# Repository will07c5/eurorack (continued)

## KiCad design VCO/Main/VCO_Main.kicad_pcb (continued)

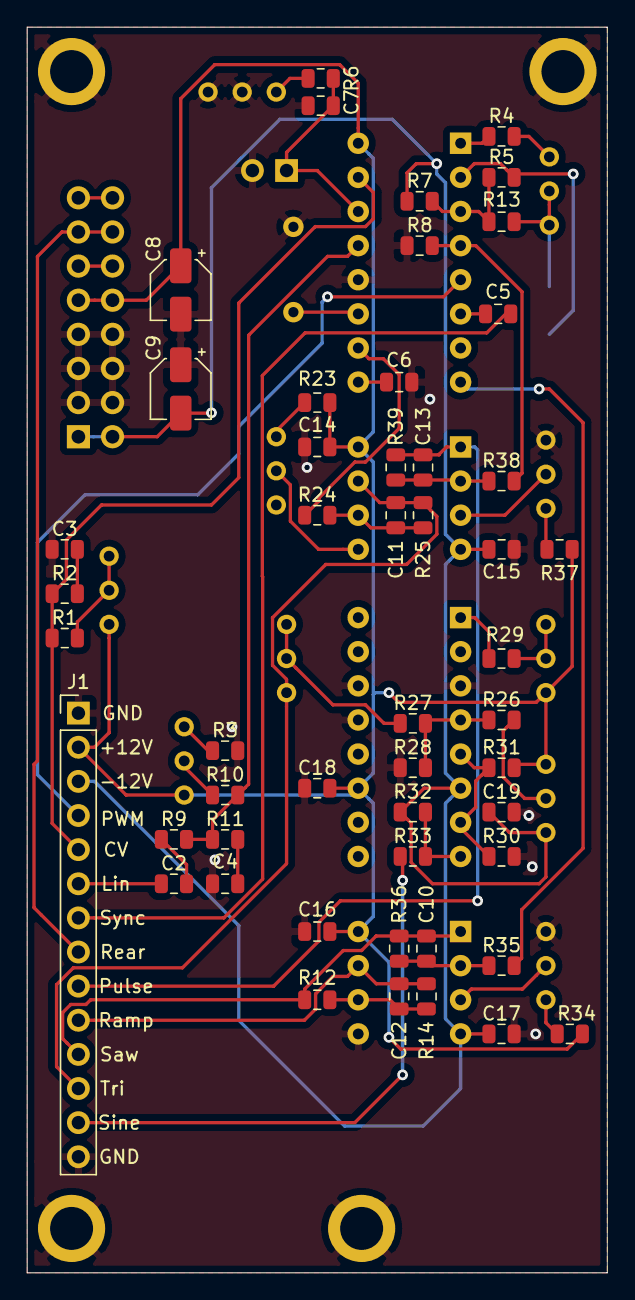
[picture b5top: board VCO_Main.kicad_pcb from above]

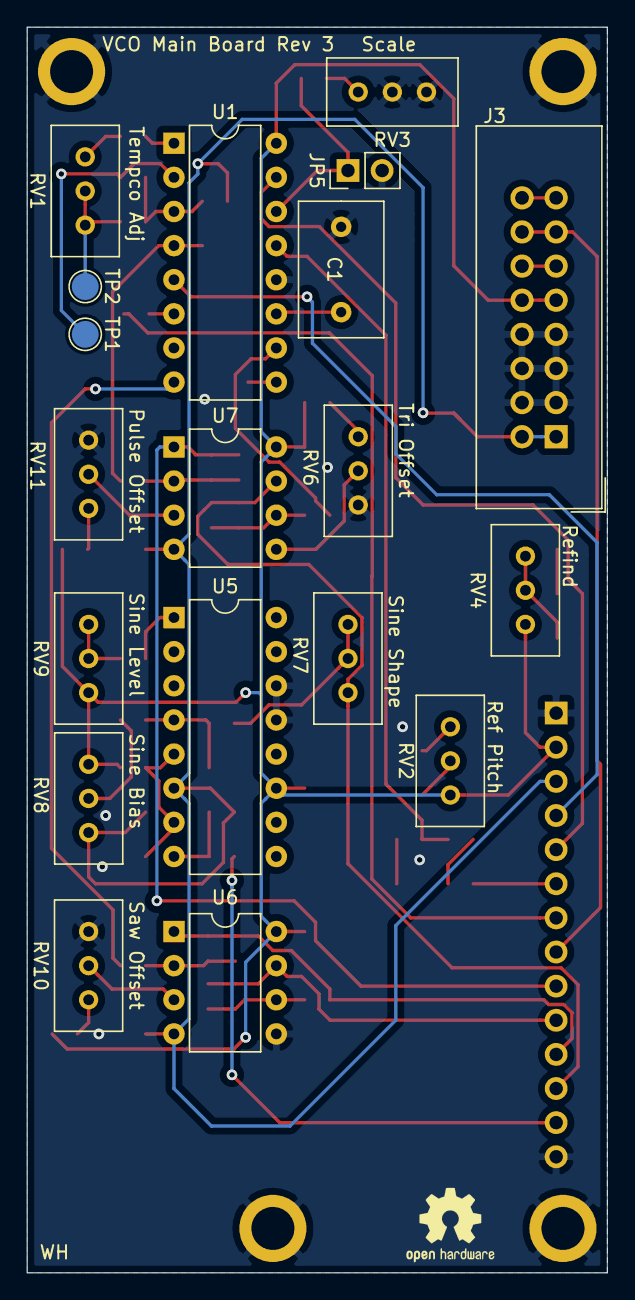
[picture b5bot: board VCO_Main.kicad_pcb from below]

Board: 2 copper layers, 43.2 x 92.7 mm, 73 parts (19 on the bottom side), 52 nets.

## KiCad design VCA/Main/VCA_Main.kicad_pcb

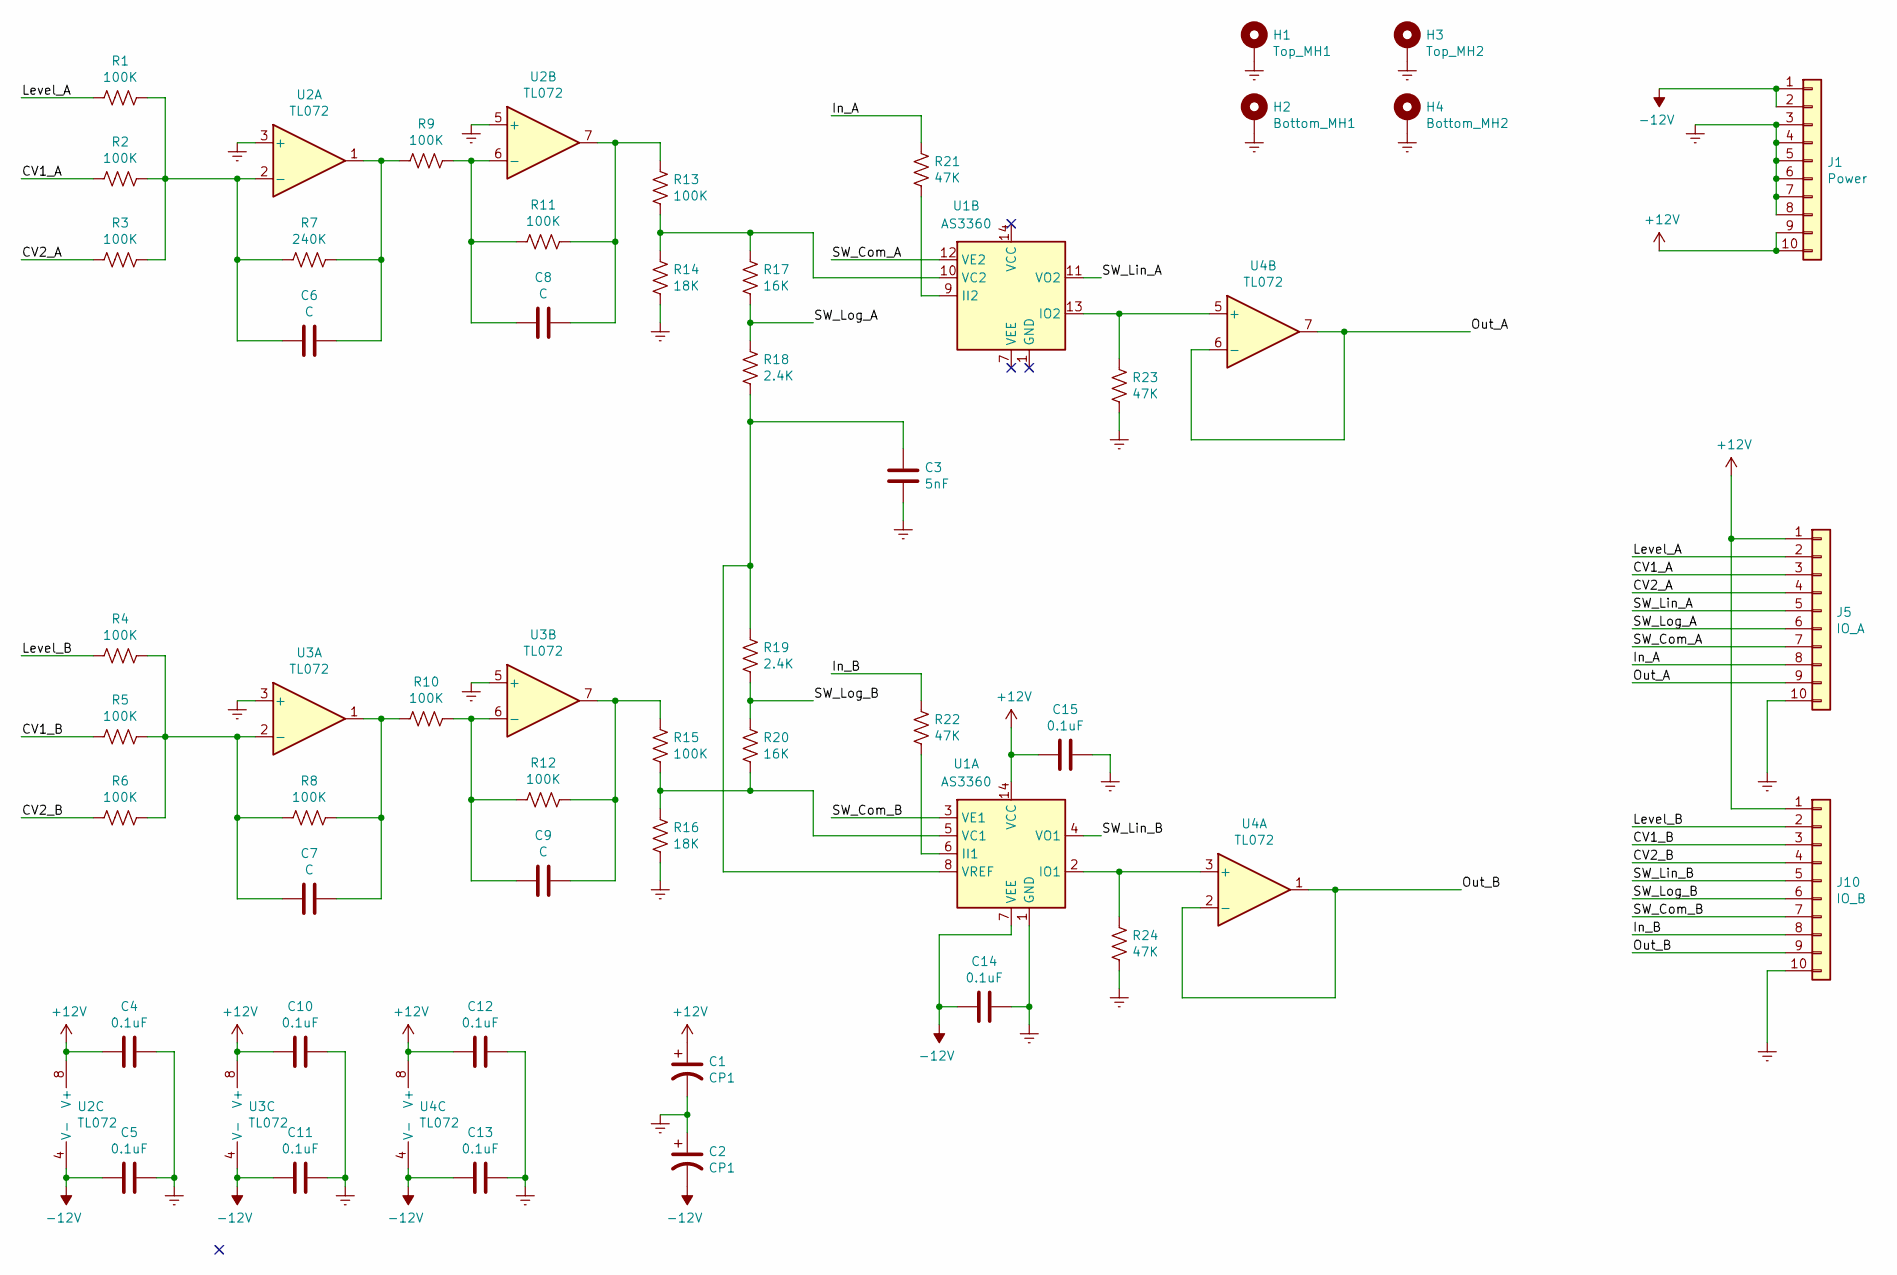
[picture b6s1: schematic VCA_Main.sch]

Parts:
C1, C2: CP1; CP_Elec_4x3
C3: 5nF; C_0805_2012Metric
C4, C5, C10, C11, C12, C13, C14, C15: 0.1uF; C_0805_2012Metric
C6, C7, C8, C9: C; C_0805_2012Metric
H1: Top_MH1; eurorack_mounting_hole
H2: Bottom_MH1; eurorack_mounting_hole
H3: Top_MH2; eurorack_mounting_hole
H4: Bottom_MH2; eurorack_mounting_hole
J1: Power; IDC-Header_2x05_P2.54mm_Vertical
J5: IO_A; PinHeader_1x10_P2.54mm_Vertical
J10: IO_B; PinHeader_1x10_P2.54mm_Vertical
R1, R2, R3, R4, R5, R6, R8, R9, R10, R11, R12, R13, R15: 100K; R_0805_2012Metric
R7: 240K; R_0805_2012Metric
R14, R16: 18K; R_0805_2012Metric
R17, R20: 16K; R_0805_2012Metric
R18, R19: 2.4K; R_0805_2012Metric
R21, R22, R23, R24: 47K; R_0805_2012Metric
U1: AS3360; DIP-14_W7.62mm
U2, U3, U4: TL072; DIP-8_W7.62mm

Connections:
+12V: C1.1, C4.2, C10.2, C12.2, C15.2, J1.9, J1.10, J5.1, J10.1, U1.14 (VCC), U2.8 (V+), U3.8 (V+), U4.8 (V+)
-12V: C2.2, C5.2, C11.2, C13.2, C14.2, J1.1, J1.2, U1.7 (VEE), U2.4 (V-), U3.4 (V-), U4.4 (V-)
/CV1_A: J5.3, R2.2
/CV1_B: J10.3, R5.2
/CV2_A: J5.4, R3.2
/CV2_B: J10.4, R6.2
/In_A: J5.8, R21.1
/In_B: J10.8, R22.1
/Level_A: J5.2, R1.2
/Level_B: J10.2, R4.2
/Out_A: J5.9, U4.6 (-), U4.7
/Out_B: J10.9, U4.1, U4.2 (-)
/SW_Com_A: J5.7, U1.12 (VE2)
/SW_Com_B: J10.7, U1.3 (VE1)
/SW_Lin_A: J5.5, U1.11 (VO2)
/SW_Lin_B: J10.5, U1.4 (VO1)
/SW_Log_A: J5.6, R17.2, R18.1
/SW_Log_B: J10.6, R19.2, R20.1
GNDREF: C1.2, C2.1, C3.2, C4.1, C5.1, C10.1, C11.1, C12.1, C13.1, C14.1, C15.1, H1.1, H2.1, H3.1, H4.1, J1.3, J1.4, J1.5, J1.6, J1.7, J1.8, J5.10, J10.10, R14.2, R16.2, R23.2, R24.2, U1.1 (GND), U2.3 (+), U2.5 (+), U3.3 (+), U3.5 (+)
unnamed: C3.1, R18.2, R19.1, U1.8 (VREF)
unnamed: C6.1, R7.1, R9.2, U2.1
unnamed: C6.2, R1.1, R2.1, R3.1, R7.2, U2.2 (-)
unnamed: C7.1, R8.1, R10.2, U3.1
unnamed: C7.2, R4.1, R5.1, R6.1, R8.2, U3.2 (-)
unnamed: C8.1, R11.1, R13.1, U2.7
unnamed: C8.2, R9.1, R11.2, U2.6 (-)
unnamed: C9.1, R12.1, R15.1, U3.7
unnamed: C9.2, R10.1, R12.2, U3.6 (-)
unnamed: R13.2, R14.1, R17.1, U1.10 (VC2)
unnamed: R15.2, R16.1, R20.2, U1.5 (VC1)
unnamed: R21.2, U1.9 (II2)
unnamed: R22.2, U1.6 (II1)
unnamed: R23.1, U1.13 (IO2), U4.5 (+)
unnamed: R24.1, U1.2 (IO1), U4.3 (+)

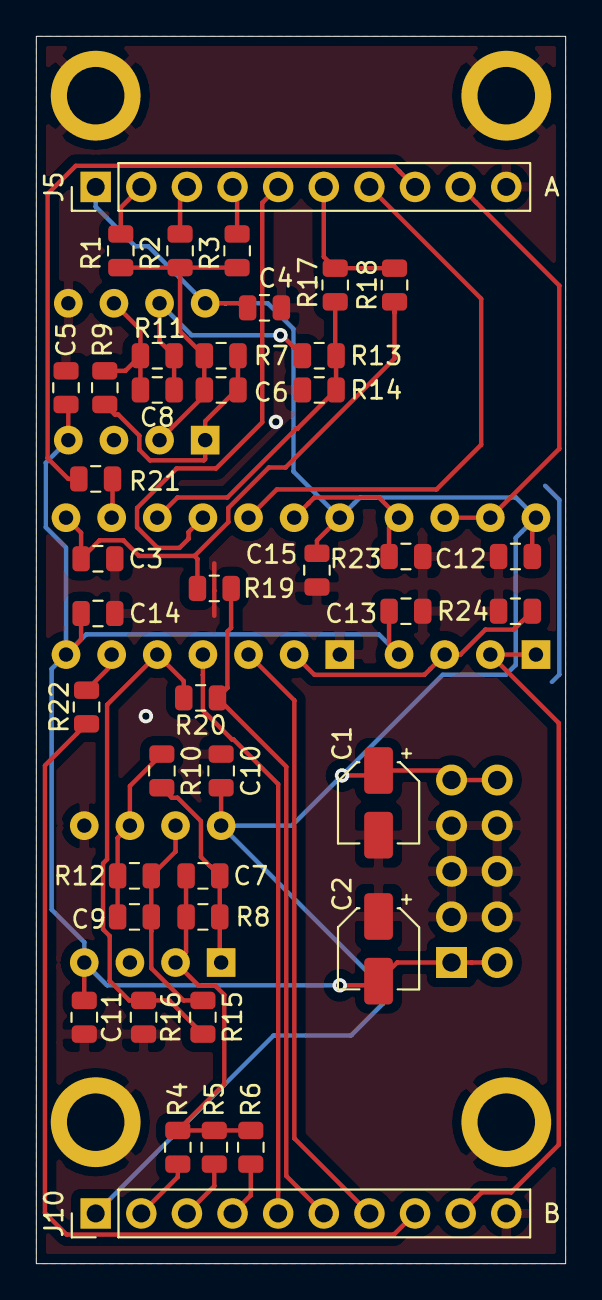
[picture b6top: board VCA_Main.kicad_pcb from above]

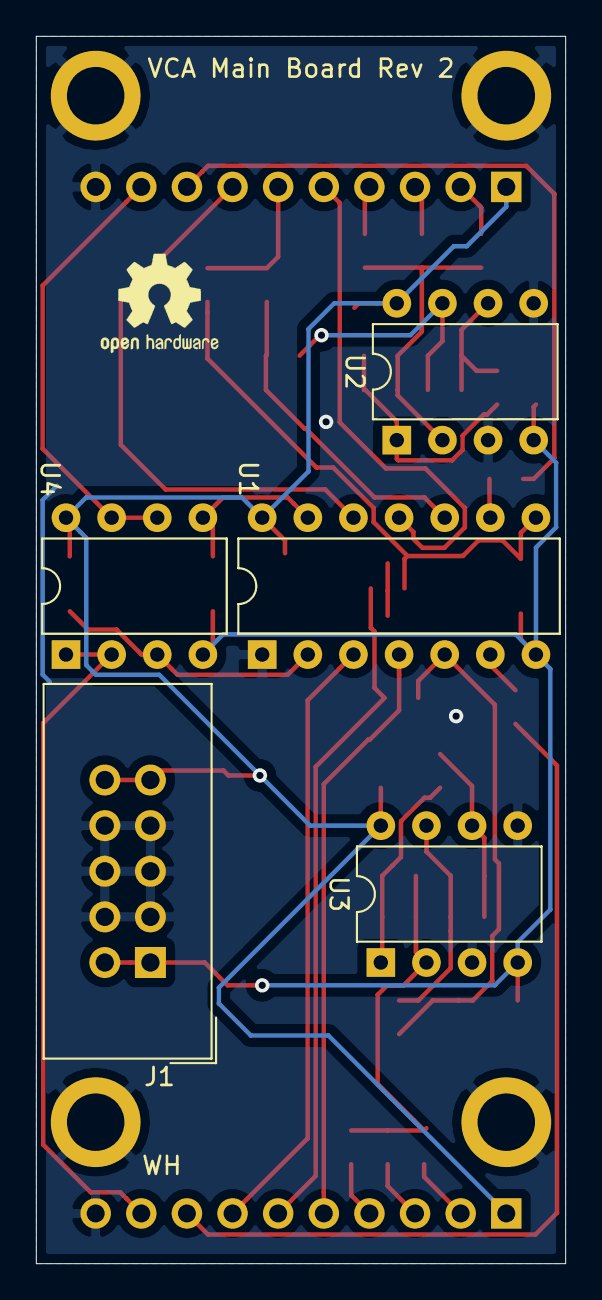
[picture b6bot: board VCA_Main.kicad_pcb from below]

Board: 2 copper layers, 29.5 x 68.3 mm, 50 parts (5 on the bottom side), 34 nets.

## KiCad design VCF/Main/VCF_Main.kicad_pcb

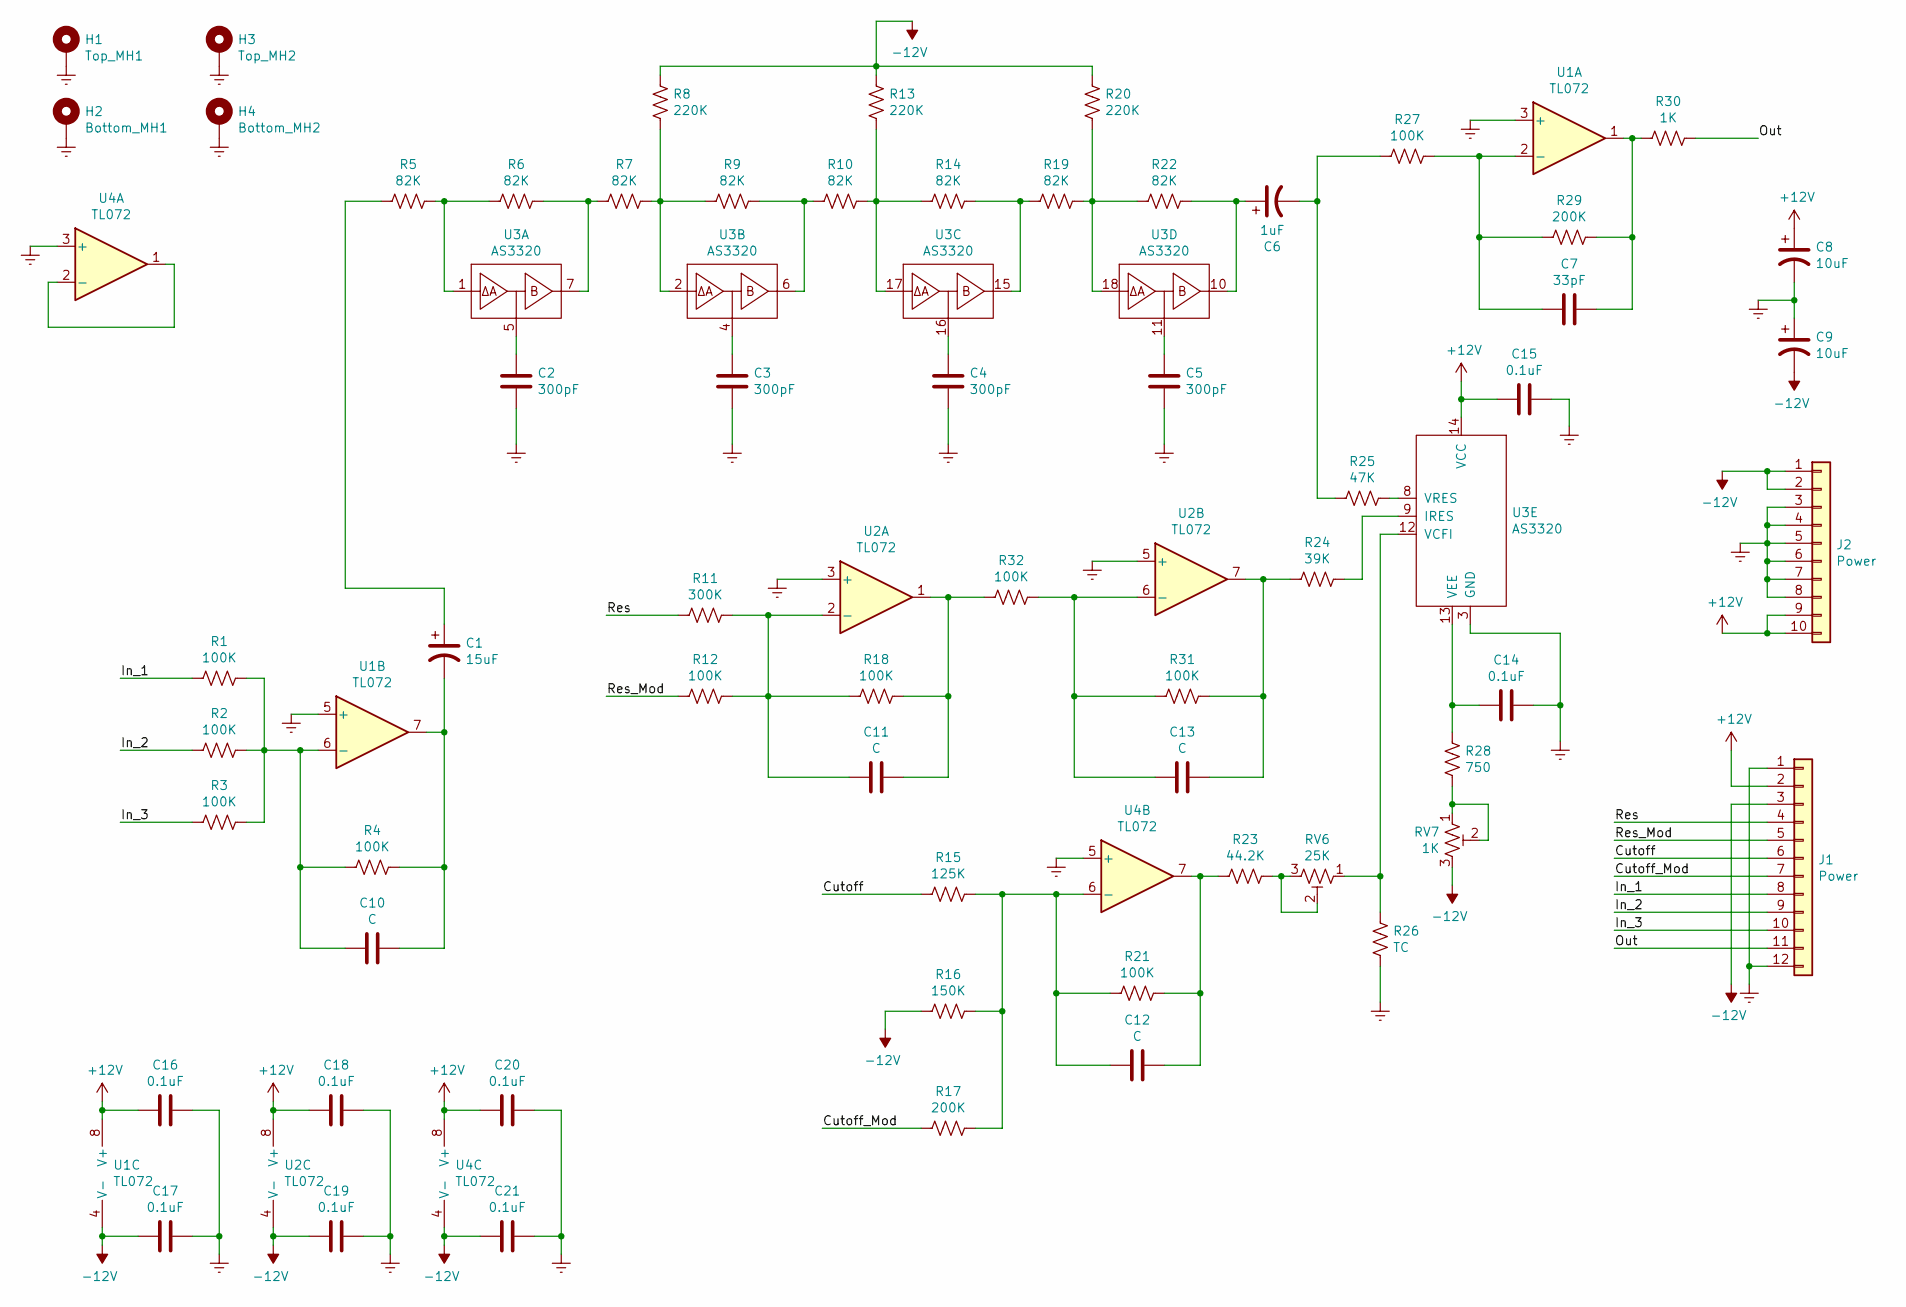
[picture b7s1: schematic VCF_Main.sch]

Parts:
C1: 15uF; CP_Elec_4x3
C2, C3, C4, C5: 300pF; Mica_Cap
C6: 1uF; CP_Elec_4x3
C7: 33pF; C_0805_2012Metric
C8, C9: 10uF; CP_Elec_4x3
C10, C11, C12, C13: C; C_0805_2012Metric
C14, C15, C16, C17, C18, C19, C20, C21: 0.1uF; C_0805_2012Metric
H1: Top_MH1; eurorack_mounting_hole
H2: Bottom_MH1; eurorack_mounting_hole
H3: Top_MH2; eurorack_mounting_hole
H4: Bottom_MH2; eurorack_mounting_hole
J1: Power; PinHeader_1x12_P2.54mm_Vertical
J2: Power; IDC-Header_2x05_P2.54mm_Vertical
R1, R2, R3, R4, R12, R18, R21, R27, R31, R32: 100K; R_0805_2012Metric
R5, R6, R7, R9, R10, R14, R19, R22: 82K; R_0805_2012Metric
R8, R13, R20: 220K; R_0805_2012Metric
R11: 300K; R_0805_2012Metric
R15: 125K; R_0805_2012Metric
R16: 150K; R_0805_2012Metric
R17, R29: 200K; R_0805_2012Metric
R23: 44.2K; R_0805_2012Metric
R24: 39K; R_0805_2012Metric
R25: 47K; R_0805_2012Metric
R26: TC; Tempco
R28: 750; R_0805_2012Metric
R30: 1K; R_0805_2012Metric
RV6: 25K; Potentiometer_Bourns_3296W_Vertical
RV7: 1K; Potentiometer_Bourns_3296W_Vertical
U1, U2, U4: TL072; DIP-8_W7.62mm
U3: AS3320; DIP-18_W7.62mm

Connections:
+12V: C8.1, C15.2, C16.2, C18.2, C20.2, J1.2, J2.9, J2.10, U1.8 (V+), U2.8 (V+), U3.14 (VCC), U4.8 (V+)
-12V: C9.2, C17.2, C19.2, C21.2, J1.3, J2.1, J2.2, R8.1, R13.1, R16.2, R20.1, RV7.3, U1.4 (V-), U2.4 (V-), U4.4 (V-)
/Cutoff: J1.6, R15.2
/Cutoff_Mod: J1.7, R17.2
/In_1: J1.8, R1.2
/In_2: J1.9, R2.2
/In_3: J1.10, R3.2
/Out: J1.11, R30.1
/Res: J1.4, R11.2
/Res_Mod: J1.5, R12.2
GNDREF: C2.2, C3.2, C4.2, C5.2, C8.2, C9.1, C14.1, C15.1, C16.1, C17.1, C18.1, C19.1, C20.1, C21.1, H1.1, H2.1, H3.1, H4.1, J1.1, J1.12, J2.3, J2.4, J2.5, J2.6, J2.7, J2.8, R26.2, U1.3 (+), U1.5 (+), U2.3 (+), U2.5 (+), U3.3 (GND), U4.3 (+), U4.5 (+)
unnamed: C1.1, R5.2
unnamed: C1.2, C10.2, R4.1, U1.7
unnamed: C2.1, U3.5
unnamed: C3.1, U3.4
unnamed: C4.1, U3.16
unnamed: C5.1, U3.11
unnamed: C6.1, R22.1, U3.10
unnamed: C6.2, R25.2, R27.2
unnamed: C7.1, R27.1, R29.2, U1.2 (-)
unnamed: C7.2, R29.1, R30.2, U1.1
unnamed: C10.1, R1.1, R2.1, R3.1, R4.2, U1.6 (-)
unnamed: C11.1, R11.1, R12.1, R18.2, U2.2 (-)
unnamed: C11.2, R18.1, R32.2, U2.1
unnamed: C12.1, R15.1, R16.1, R17.1, R21.2, U4.6 (-)
unnamed: C12.2, R21.1, R23.2, U4.7
unnamed: C13.1, R31.2, R32.1, U2.6 (-)
unnamed: C13.2, R24.2, R31.1, U2.7
unnamed: C14.2, R28.1, U3.13 (VEE)
unnamed: R5.1, R6.2, U3.1
unnamed: R6.1, R7.2, U3.7
unnamed: R7.1, R8.2, R9.2, U3.2
unnamed: R10.1, R13.2, R14.2, U3.17
unnamed: R9.1, R10.2, U3.6
unnamed: R14.1, R19.2, U3.15
unnamed: R19.1, R20.2, R22.2, U3.18
unnamed: R23.1, RV6.2, RV6.3
unnamed: R24.1, U3.9 (IRES)
unnamed: R25.1, U3.8 (VRES)
unnamed: R26.1, RV6.1, U3.12 (VCFI)
unnamed: R28.2, RV7.1, RV7.2
unnamed: U4.1, U4.2 (-)

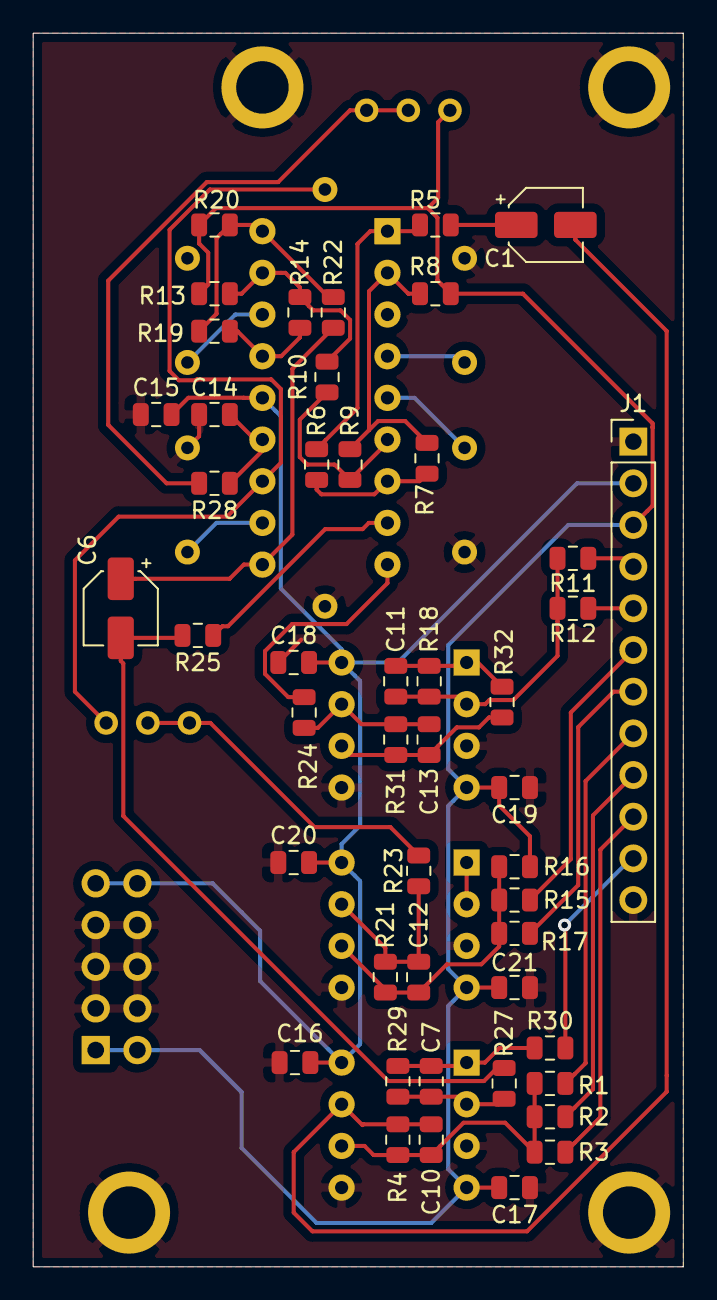
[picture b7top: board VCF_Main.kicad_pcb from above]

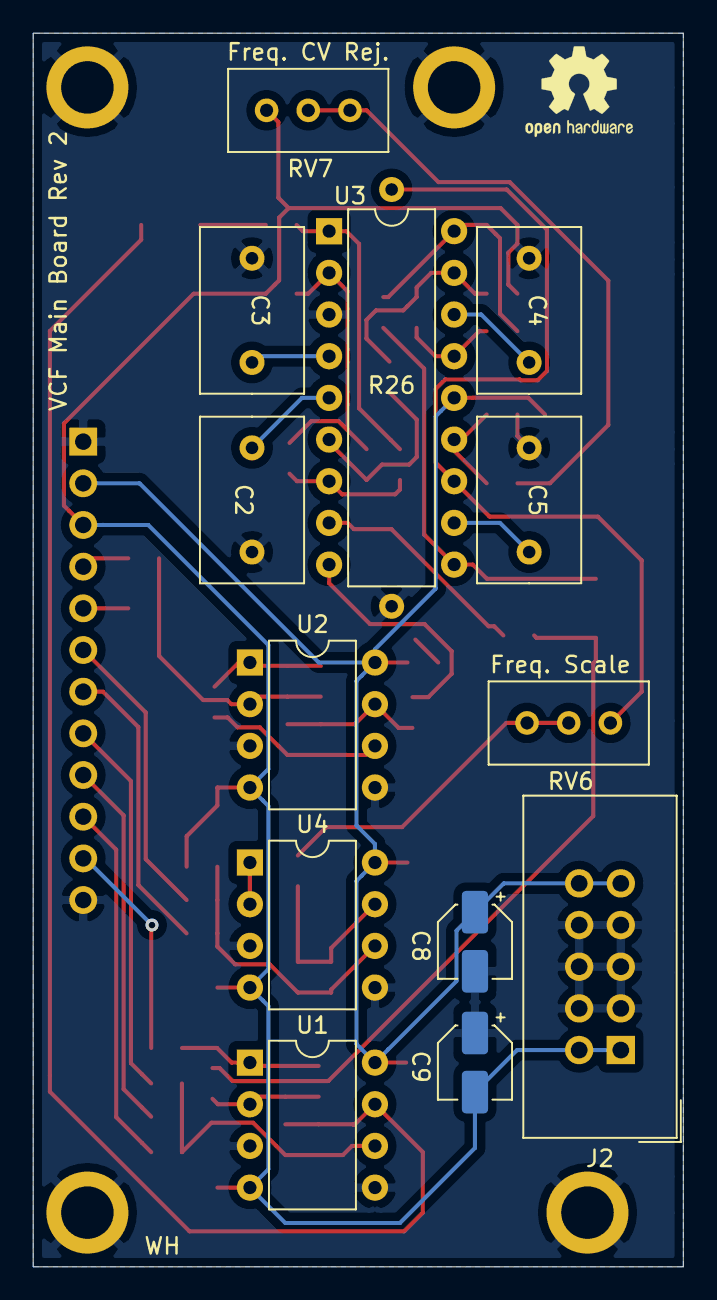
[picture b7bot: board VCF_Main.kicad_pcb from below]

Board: 2 copper layers, 39.6 x 75.2 mm, 65 parts (14 on the bottom side), 42 nets.

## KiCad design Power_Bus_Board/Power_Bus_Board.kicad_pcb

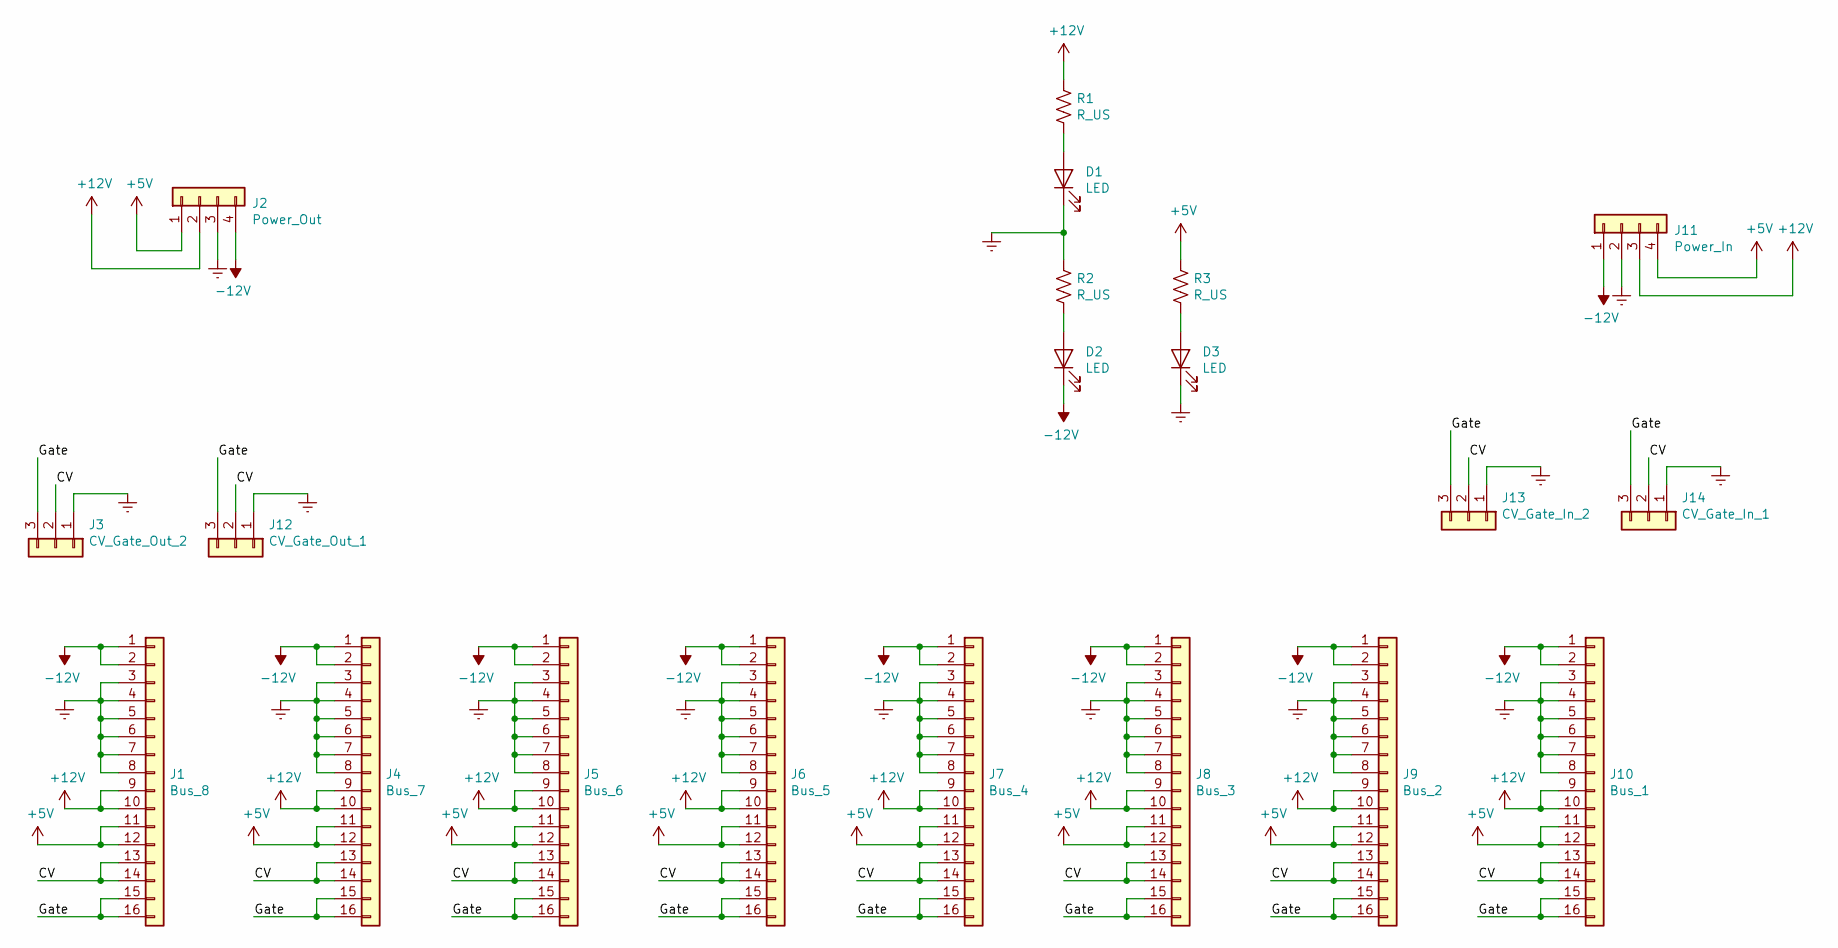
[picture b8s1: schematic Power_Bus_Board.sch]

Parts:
D1, D2, D3: LED; LED_D5.0mm
J1: Bus_8; IDC-Header_2x08_P2.54mm_Vertical
J2: Power_Out; TerminalBlock_bornier-4_P5.08mm
J3: CV_Gate_Out_2; PinHeader_1x03_P2.54mm_Vertical
J4: Bus_7; IDC-Header_2x08_P2.54mm_Vertical
J5: Bus_6; IDC-Header_2x08_P2.54mm_Vertical
J6: Bus_5; IDC-Header_2x08_P2.54mm_Vertical
J7: Bus_4; IDC-Header_2x08_P2.54mm_Vertical
J8: Bus_3; IDC-Header_2x08_P2.54mm_Vertical
J9: Bus_2; IDC-Header_2x08_P2.54mm_Vertical
J10: Bus_1; IDC-Header_2x08_P2.54mm_Vertical
J11: Power_In; TerminalBlock_bornier-4_P5.08mm
J12: CV_Gate_Out_1; TerminalBlock_bornier-3_P5.08mm
J13: CV_Gate_In_2; PinHeader_1x03_P2.54mm_Vertical
J14: CV_Gate_In_1; TerminalBlock_bornier-3_P5.08mm
R1, R2, R3: R_US; R_0805_2012Metric

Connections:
+5V: J1.11, J1.12, J2.1, J4.11, J4.12, J5.11, J5.12, J6.11, J6.12, J7.11, J7.12, J8.11, J8.12, J9.11, J9.12, J10.11, J10.12, J11.4, R3.1
+12V: J1.9, J1.10, J2.2, J4.9, J4.10, J5.9, J5.10, J6.9, J6.10, J7.9, J7.10, J8.9, J8.10, J9.9, J9.10, J10.9, J10.10, J11.3, R1.1
-12V: D2.1 (K), J1.1, J1.2, J2.4, J4.1, J4.2, J5.1, J5.2, J6.1, J6.2, J7.1, J7.2, J8.1, J8.2, J9.1, J9.2, J10.1, J10.2, J11.1
/CV: J1.13, J1.14, J3.2, J4.13, J4.14, J5.13, J5.14, J6.13, J6.14, J7.13, J7.14, J8.13, J8.14, J9.13, J9.14, J10.13, J10.14, J12.2, J13.2, J14.2
/Gate: J1.15, J1.16, J3.3, J4.15, J4.16, J5.15, J5.16, J6.15, J6.16, J7.15, J7.16, J8.15, J8.16, J9.15, J9.16, J10.15, J10.16, J12.3, J13.3, J14.3
GNDREF: D1.1 (K), D3.1 (K), J1.3, J1.4, J1.5, J1.6, J1.7, J1.8, J2.3, J3.1, J4.3, J4.4, J4.5, J4.6, J4.7, J4.8, J5.3, J5.4, J5.5, J5.6, J5.7, J5.8, J6.3, J6.4, J6.5, J6.6, J6.7, J6.8, J7.3, J7.4, J7.5, J7.6, J7.7, J7.8, J8.3, J8.4, J8.5, J8.6, J8.7, J8.8, J9.3, J9.4, J9.5, J9.6, J9.7, J9.8, J10.3, J10.4, J10.5, J10.6, J10.7, J10.8, J11.2, J12.1, J13.1, J14.1, R2.1
unnamed: D1.2 (A), R1.2
unnamed: D2.2 (A), R2.2
unnamed: D3.2 (A), R3.2

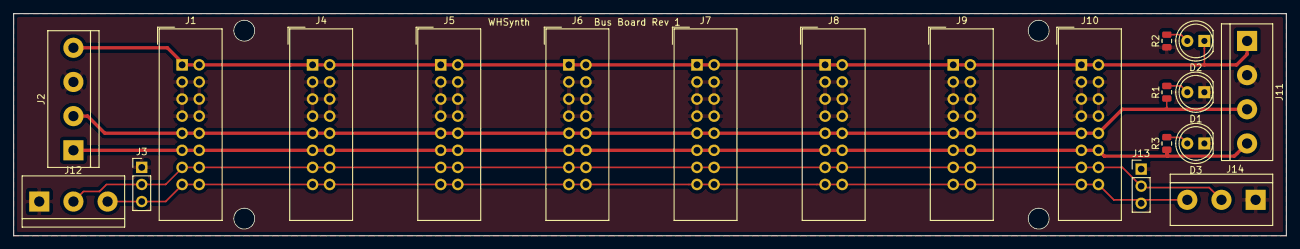
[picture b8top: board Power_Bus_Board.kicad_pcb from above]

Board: 2 copper layers, 189.2 x 33.0 mm, 20 parts (0 on the bottom side), 9 nets.

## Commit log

2019-09-10 AS3340_VCO rev1 (with SMD ICs)
2019-09-10 AS3340_VCO rev 2 AS3310_ADSR rev 1 AS3320_VCF rev 1 AS3360_VCA rev 1 ER_Bus_Board rev 1
2019-09-10 Adding change log and known issues files
2019-09-13 Add front panel and IO boards for VCO
2019-09-13 Re-do VCO board to support new front panel board
2019-09-13 Update known issues doc
2019-09-14 Adding front panel for ADSR
2019-09-14 Combine IO and main ADSR boards
2019-09-20 Adding front panel board for VCA
2019-09-20 Organize boards in a more sane way.
2019-09-20 Update known issues.
2019-09-21 Add VCA IO board
2019-09-21 Update known issues
2019-09-21 Update front panel to match IO board
2019-09-21 Re-doing VCA board to be compatible with new front panel design.
2019-09-21 Add readme
2019-09-24 Adding front panel board for VCF
2019-09-25 Move footprints to common folder and update known issues
2019-09-25 Add IO board for VCF
2019-09-25 Update VCF main board for new front panel
2019-09-25 Add mounting holes for main board
2019-09-25 Fix envelope generator front panel size and alignment with IO board.
2019-09-26 Clean up VCA boards
2019-09-26 Clean up envelope generator boards
2019-09-26 Clean up VCF boards
2019-09-26 Resolve most of the issues in known_issues.txt
2019-09-26 Fix minor issues with VCO board
2019-09-26 Fix inverted resonance control input
2019-10-03 Bunch of bug fixes and tweaks
2019-10-03 Add resistor divider for Sync input and some capacitors.
2019-10-07 Clean up layout of VCF board
2019-10-08 Make VCF front panel bigger. Re-align IO and FP boards.
2019-10-08 Clean up layout of VCO board
2019-10-08 Update tick marks footprint
2019-10-09 Clean up layout of VCA board
2019-10-09 Clean up envelope gen board
2019-10-10 Added Gerber files
2019-12-01 Fix resistor values for ADSR Sustain
2019-12-22 Add AS3394e to library
2019-12-22 Fix backwards knobs
